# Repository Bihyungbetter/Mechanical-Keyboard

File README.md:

# Mechanical Keyboard

## Overview

This Mechanical Keyboard is a custom 75-key Alice mechanical keyboard built around a Raspberry Pi Pico / RP2040. It has a 5×15 key matrix, per-key SK6812 MINI-E RGB lighting, an EC11 rotary encoder with push switch, and a 128×32 I2C OLED display. I learned how to stitch together different parts, and I made this in hopes of a more ergonomic keyboard. 

I estimate I need 125$ for funding. Any extra funds will be returned to Hack Club

I do plan to make more unique designs and carvings in the CAD, but I want to first get it approved. School starts for me soon, so it's important for me to get this done asap :D. 
## Features

- 75 MX-compatible hot-swap switch positions
- RP2040 controller
- 75 SK6812 MINI-E addressable RGB LEDs
- Rotary encoder with volume control and mute push switch
- 128×32 I2C OLED display
- QMK firmware with a base layer and function/RGB layer

Onshape Link: https://cad.onshape.com/documents/8ad6bc956480bc630ab8271b/w/5b6e3b74d25b2afffc5b1596/e/df48eba2c3a944c445852ffe?renderMode=0&uiState=6ad977a7a138a0b5e7c4d2a0

## Repository layout

- `pcb/` — KiCad PCB, schematic, project, and lighting schematic
- `cad/` — The Entire CAD Assembly for the Keyboard
- `firmware/` — board-specific QMK sources and the compiled UF2
- `production/` — Gerber and drill files (gerber.zip) for PCB fabrication

## Pictures

## BOM

| Item | Part / Variant | Qty | Unit (USD) | Total (USD) | Link |
|---|---|---:|---:|---:|---|
| Raspberry Pi Pico | Raspberry Pi SC0915 (RP2040) | 1 | $4.59 | $4.59 | [DigiKey](https://www.digikey.com/en/products/detail/raspberry-pi/SC0915/13624793) |
| 1N4148 diode (DO-35) | onsemi 1N4148TA | 100 | $0.0336 | $3.36 | [DigiKey](https://www.digikey.com/en/products/detail/onsemi/1N4148TA/1532747) |
| Kailh MX hot-swap socket | Kailh CPG151101S11 | 80 | $0.10 | $8.00 | [KBDfans](https://kbdfans.com/products/mechanical-keyboard-switches-kailh-pcb-socket?variant=39678399381643) |
| EPOMAKER Creamy Jade switch | Creamy Jade Switch Set, 100 pcs (5-pin MX linear) | 1 | $19.99 | $19.99 | [EPOMAKER](https://epomaker.com/products/epomaker-creamy-jade-switch-set?variant=49273295831348) |
| SK6812 MINI-E RGB LED | SK-6812 MINI-E RGB LEDs, 25-pack | 4 | $5.99 | $23.96 | [Keebio](https://keeb.io/products/sk-6812-mini-e-rgb-leds-12-pack) |
| 0.91in 128x32 I2C OLED | HiLetgo 0.91in SSD1306 128x32 I2C | 1 | $6.49 | $6.49 | [Amazon](https://www.amazon.com/dp/B01N0KIVUX) |
| EC11 rotary encoder with push switch | Rotary Encoder - EC11, 20mm knurled shaft | 1 | $1.99 | $1.99 | [Keebio](https://keeb.io/products/rotary-encoder-ec11) |
| PCB-mount MX stabilizer | Cherry MX Stabilizer, 2u PCB Mount (2-pack) | 2 | $3.98 | $7.96 | [Keebio](https://keeb.io/products/cherry-mx-stabilizer?variant=39511997382750) |
| 100 nF capacitor (0805) | Samsung CL21B104KBCNNNC | 20 | $0.045 | $0.90 | [DigiKey](https://www.digikey.com/en/products/detail/samsung-electro-mechanics/CL21B104KBCNNNC/3886661) |
| 100 uF capacitor (1206, 10 V) | Murata GRM31CR61A107MEA8L | 2 | $0.55 | $1.10 | [DigiKey](https://www.digikey.com/en/products/detail/murata-electronics/GRM31CR61A107MEA8L/16033775) |
| 330 ohm resistor (0805) | Yageo RC0805FR-07330RL | 10 | $0.038 | $0.38 | [DigiKey](https://www.digikey.com/en/products/detail/yageo/RC0805FR-07330RL/727866) |
| Keycaps | Daylight PBT translucent keycaps, OEM profile, 135 keys - TopPrint White (keycaps only) | 1 | $11.15 | $11.15 | [AliExpress](https://www.aliexpress.us/item/3256810405041338.html) |
| PCB (5 pcs) | JLCPCB 360 x 155 mm, 2-layer, 1.6 mm FR-4 | 1 | $30.90 | $30.90 | [JLCPCB](https://cart.jlcpcb.com/quote) |
| **Total** | | | | **$120.77** | |

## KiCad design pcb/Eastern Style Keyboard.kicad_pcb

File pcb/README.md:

# PCB files

Open `Eastern Style Keyboard.kicad_pro` in KiCad. `Eastern Style Keyboard.kicad_pcb` is the board layout, and the two schematic files contain the main design and lighting-related circuitry.

The fabrication-ready outputs are in `../production/gerber.zip`.

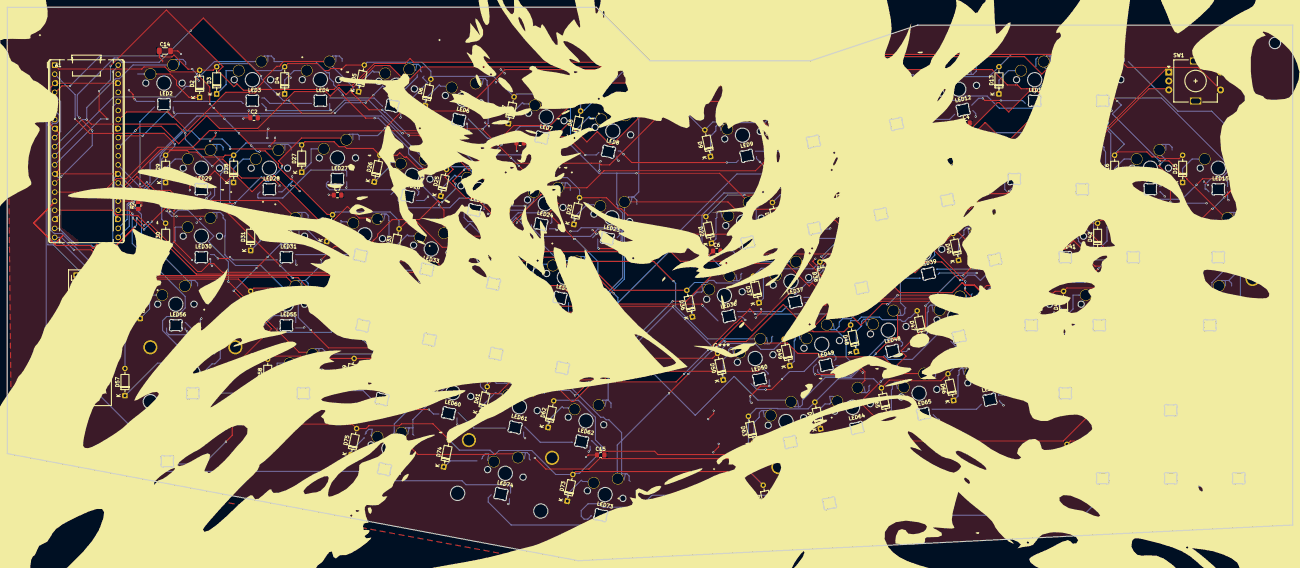
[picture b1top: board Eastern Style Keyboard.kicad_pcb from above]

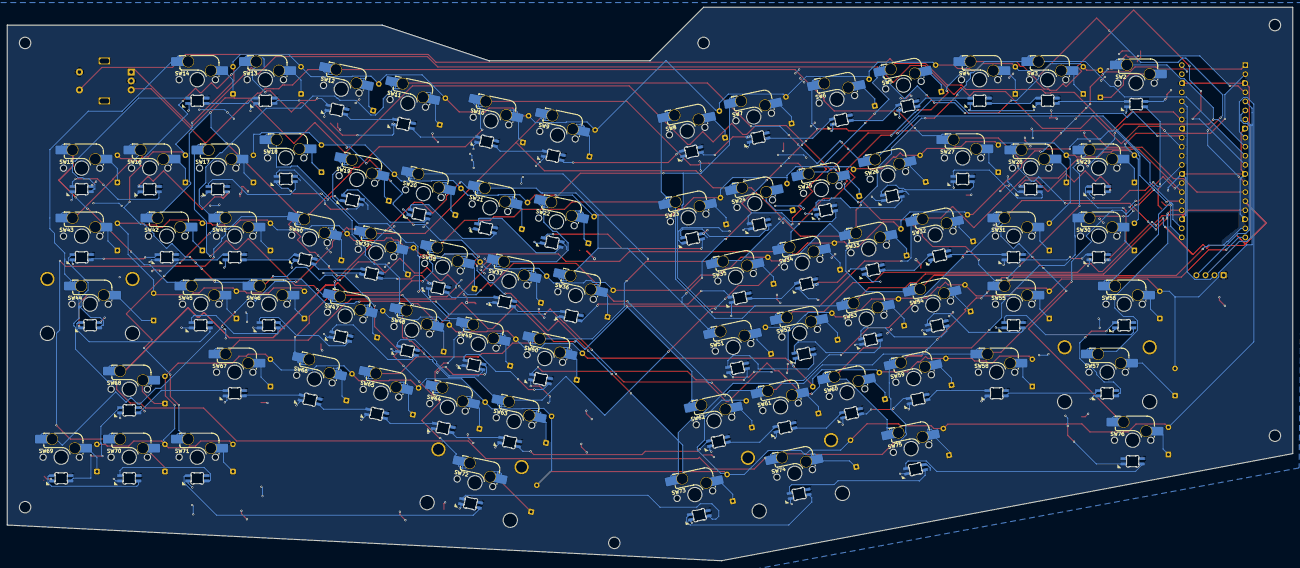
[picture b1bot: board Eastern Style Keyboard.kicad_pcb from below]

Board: 2 copper layers, 360.0 x 155.0 mm, 255 parts (75 on the bottom side), 179 nets.

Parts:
A1: RaspberryPi_Pico; RaspberryPi_Pico_Common_THT
C2, C3, C4, C5, C6, C7, C8, C9, C10, C11, C12, C13, C15, C16, C17: 100nF; C_0805_2012Metric_Pad1.18x1.45mm_HandSolder
C14: 100µF 10V; C_1206_3216Metric_Pad1.33x1.80mm_HandSolder
D2, D3, D4, D5, D6, D7, D8, D9, D10, D11, D12, D13, D14, D15, D16, D17, D18, D19, D20, D21, D22, D23, D24, D25, D26, D27, D28, D29, D30, D31, D32, D33, D34, D35, D36, D37, D38, D39, D40, D41, D42, D43, D44, D45, D46, D47, D48, D49, D50, D51, D52, D53, D54, D55, D56, D57, D58, D59, D60, D61, D62, D63, D64, D65, D66, D67, D68, D69, D70, D71, D72, D73, D74, D75, D76: 1N4148; D_DO-35_SOD27_P7.62mm_Horizontal
H1, H2, H3, H4, H5, H6: MountingHole; MountingHole_3.2mm_M3
LED2, LED3, LED4, LED5, LED6, LED7, LED8, LED9, LED10, LED11, LED12, LED13, LED14, LED15, LED16, LED17, LED18, LED19, LED20, LED21, LED22, LED23, LED24, LED25, LED26, LED27, LED28, LED29, LED30, LED31, LED32, LED33, LED34, LED35, LED36, LED37, LED38, LED39, LED40, LED41, LED42, LED43, LED44, LED45, LED46, LED47, LED48, LED49, LED50, LED51, LED52, LED53, LED54, LED55, LED56, LED57, LED58, LED59, LED60, LED61, LED62, LED63, LED64, LED65, LED66, LED67, LED68, LED69, LED70, LED71, LED72, LED73, LED74, LED75, LED76: SK6812MINI-E; SK6812MINI-E_fixed
R2: 330 Ω; R_0805_2012Metric_Pad1.20x1.40mm_HandSolder
S1: MX_stab; STAB_MX_P_2u
S2: MX_stab; STAB_MX_P_2.75u
S3, S4: MX_stab; STAB_MX_P_2.25u
SW1: RotaryEncoder_Switch; RotaryEncoder_Alps_EC11E-Switch_Vertical_H20mm
SW2, SW3, SW4, SW5, SW6, SW7, SW8, SW9, SW10, SW11, SW12, SW13, SW14, SW15, SW16, SW17, SW18, SW19, SW20, SW21, SW22, SW23, SW24, SW25, SW26, SW27, SW28, SW29, SW30, SW31, SW32, SW33, SW34, SW35, SW36, SW37, SW38, SW39, SW40, SW41, SW42, SW43, SW44, SW45, SW46, SW47, SW48, SW49, SW50, SW51, SW52, SW53, SW54, SW55, SW56, SW57, SW58, SW59, SW60, SW61, SW62, SW63, SW64, SW65, SW66, SW67, SW68, SW69, SW70, SW71, SW72, SW73, SW74, SW75, SW76: SW_Push; SW_MX_HS_CPG151101S11_1u
U1: ER_OLEDM0.91_1x-I2C

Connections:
+3.3V: A1.36 (3V3), U1.2 (VCC)
Column 0: A1.10 (GPIO7), SW2.2, SW17.2, SW32.2, SW47.2, SW62.2
Column 1: A1.11 (GPIO8), SW3.2, SW18.2, SW33.2, SW48.2, SW63.2
Column 2: A1.12 (GPIO9), SW4.2, SW19.2, SW34.2, SW49.2, SW64.2
Column 3: A1.14 (GPIO10), SW5.2, SW20.2, SW35.2, SW50.2, SW65.2
Column 4: A1.15 (GPIO11), SW6.2, SW21.2, SW36.2, SW51.2, SW66.2
Column 5: A1.16 (GPIO12), SW7.2, SW22.2, SW37.2, SW52.2, SW67.2
Column 6: A1.17 (GPIO13), SW8.2, SW23.2, SW38.2, SW53.2, SW68.2
Column 7: A1.19 (GPIO14), SW9.2, SW24.2, SW39.2, SW54.2, SW69.2
Column 8: A1.20 (GPIO15), SW10.2, SW25.2, SW40.2, SW55.2, SW70.2
Column 9: A1.22 (GPIO17), SW11.2, SW26.2, SW41.2, SW56.2, SW71.2
Column 10: A1.24 (GPIO18), SW12.2, SW27.2, SW42.2, SW57.2, SW72.2
Column 11: A1.25 (GPIO19), SW13.2, SW28.2, SW43.2, SW58.2, SW73.2
Column 12: A1.26 (GPIO20), SW14.2, SW29.2, SW44.2, SW59.2, SW74.2
Column 13: A1.27 (GPIO21), SW15.2, SW30.2, SW45.2, SW60.2, SW75.2
Column 14: A1.29 (GPIO22), SW16.2, SW31.2, SW46.2, SW61.2, SW76.2
GND: A1.3 (GND), A1.8 (GND), A1.13 (GND), A1.18 (GND), A1.23 (GND), A1.28 (GND), A1.38 (GND), C2.1, C3.1, C4.1, C5.1, C6.1, C7.1, C8.1, C9.1, C10.1, C11.1, C12.1, C13.1, C14.2, C15.1, C16.1, C17.1, LED2.1 (VSS), LED3.1 (VSS), LED4.1 (VSS), LED5.1 (VSS), LED6.1 (VSS), LED7.1 (VSS), LED8.1 (VSS), LED9.1 (VSS), LED10.1 (VSS), LED11.1 (VSS), LED12.1 (VSS), LED13.1 (VSS), LED14.1 (VSS), LED15.1 (VSS), LED16.1 (VSS), LED17.1 (VSS), LED18.1 (VSS), LED19.1 (VSS), LED20.1 (VSS), LED21.1 (VSS), LED22.1 (VSS), LED23.1 (VSS), LED24.1 (VSS), LED25.1 (VSS), LED26.1 (VSS), LED27.1 (VSS), LED28.1 (VSS), LED29.1 (VSS), LED30.1 (VSS), LED31.1 (VSS), LED32.1 (VSS), LED33.1 (VSS), LED34.1 (VSS), LED35.1 (VSS), LED36.1 (VSS), LED37.1 (VSS), LED38.1 (VSS), LED39.1 (VSS), LED40.1 (VSS), LED41.1 (VSS), LED42.1 (VSS), LED43.1 (VSS), LED44.1 (VSS), LED45.1 (VSS), LED46.1 (VSS), LED47.1 (VSS), LED48.1 (VSS), LED49.1 (VSS), LED50.1 (VSS), LED51.1 (VSS), LED52.1 (VSS), LED53.1 (VSS), LED54.1 (VSS), LED55.1 (VSS), LED56.1 (VSS), LED57.1 (VSS), LED58.1 (VSS), LED59.1 (VSS), LED60.1 (VSS), LED61.1 (VSS), LED62.1 (VSS), LED63.1 (VSS), LED64.1 (VSS), LED65.1 (VSS), LED66.1 (VSS), LED67.1 (VSS), LED68.1 (VSS), LED69.1 (VSS), LED70.1 (VSS), LED71.1 (VSS), LED72.1 (VSS), LED73.1 (VSS), LED74.1 (VSS), LED75.1 (VSS), LED76.1 (VSS), SW1.C, SW1.S2, U1.1 (GND)
KnobA: A1.31 (GPIO26_ADC0), SW1.A
KnobB: A1.32 (GPIO27_ADC1), SW1.B
LED Power: A1.40 (VBUS), C2.2, C3.2, C4.2, C5.2, C6.2, C7.2, C8.2, C9.2, C10.2, C11.2, C12.2, C13.2, C14.1, C15.2, C16.2, C17.2, LED2.3 (VDD), LED3.3 (VDD), LED4.3 (VDD), LED5.3 (VDD), LED6.3 (VDD), LED7.3 (VDD), LED8.3 (VDD), LED9.3 (VDD), LED10.3 (VDD), LED11.3 (VDD), LED12.3 (VDD), LED13.3 (VDD), LED14.3 (VDD), LED15.3 (VDD), LED16.3 (VDD), LED17.3 (VDD), LED18.3 (VDD), LED19.3 (VDD), LED20.3 (VDD), LED21.3 (VDD), LED22.3 (VDD), LED23.3 (VDD), LED24.3 (VDD), LED25.3 (VDD), LED26.3 (VDD), LED27.3 (VDD), LED28.3 (VDD), LED29.3 (VDD), LED30.3 (VDD), LED31.3 (VDD), LED32.3 (VDD), LED33.3 (VDD), LED34.3 (VDD), LED35.3 (VDD), LED36.3 (VDD), LED37.3 (VDD), LED38.3 (VDD), LED39.3 (VDD), LED40.3 (VDD), LED41.3 (VDD), LED42.3 (VDD), LED43.3 (VDD), LED44.3 (VDD), LED45.3 (VDD), LED46.3 (VDD), LED47.3 (VDD), LED48.3 (VDD), LED49.3 (VDD), LED50.3 (VDD), LED51.3 (VDD), LED52.3 (VDD), LED53.3 (VDD), LED54.3 (VDD), LED55.3 (VDD), LED56.3 (VDD), LED57.3 (VDD), LED58.3 (VDD), LED59.3 (VDD), LED60.3 (VDD), LED61.3 (VDD), LED62.3 (VDD), LED63.3 (VDD), LED64.3 (VDD), LED65.3 (VDD), LED66.3 (VDD), LED67.3 (VDD), LED68.3 (VDD), LED69.3 (VDD), LED70.3 (VDD), LED71.3 (VDD), LED72.3 (VDD), LED73.3 (VDD), LED74.3 (VDD), LED75.3 (VDD), LED76.3 (VDD)
Led S: A1.21 (GPIO16), R2.2
unnamed: A1.6 (GPIO4), U1.4 (SDA)
unnamed: A1.7 (GPIO5), U1.3 (SCL)
unnamed: D2.1 (K), SW2.1
unnamed: D3.1 (K), SW3.1
unnamed: D4.1 (K), SW4.1
unnamed: D5.1 (K), SW5.1
unnamed: D6.1 (K), SW6.1
unnamed: D7.1 (K), SW7.1
unnamed: D8.1 (K), SW8.1
unnamed: D9.1 (K), SW9.1
unnamed: D10.1 (K), SW10.1
unnamed: D11.1 (K), SW11.1
unnamed: D12.1 (K), SW12.1
unnamed: D13.1 (K), SW13.1
unnamed: D14.1 (K), SW14.1
unnamed: D15.1 (K), SW15.1
unnamed: D16.1 (K), SW16.1
unnamed: D17.1 (K), SW17.1
unnamed: D18.1 (K), SW18.1
unnamed: D19.1 (K), SW19.1
unnamed: D20.1 (K), SW20.1
unnamed: D21.1 (K), SW21.1
unnamed: D22.1 (K), SW22.1
unnamed: D23.1 (K), SW23.1
unnamed: D24.1 (K), SW24.1
unnamed: D25.1 (K), SW25.1
unnamed: D26.1 (K), SW26.1
unnamed: D27.1 (K), SW27.1
unnamed: D28.1 (K), SW28.1
unnamed: D29.1 (K), SW29.1
unnamed: D30.1 (K), SW30.1
unnamed: D31.1 (K), SW31.1
unnamed: D32.1 (K), SW32.1
unnamed: D33.1 (K), SW33.1
unnamed: D34.1 (K), SW34.1
unnamed: D35.1 (K), SW35.1
unnamed: D36.1 (K), SW36.1
unnamed: D37.1 (K), SW37.1
unnamed: D38.1 (K), SW38.1
unnamed: D39.1 (K), SW39.1
unnamed: D40.1 (K), SW40.1
unnamed: D41.1 (K), SW41.1
unnamed: D42.1 (K), SW42.1
unnamed: D43.1 (K), SW43.1
unnamed: D44.1 (K), SW44.1
unnamed: D45.1 (K), SW45.1
unnamed: D46.1 (K), SW46.1
unnamed: D47.1 (K), SW47.1
unnamed: D48.1 (K), SW48.1
unnamed: D49.1 (K), SW49.1
unnamed: D50.1 (K), SW50.1
unnamed: D51.1 (K), SW51.1
unnamed: D52.1 (K), SW52.1
unnamed: D53.1 (K), SW53.1
unnamed: D54.1 (K), SW54.1
unnamed: D55.1 (K), SW55.1
unnamed: D56.1 (K), SW56.1
unnamed: D57.1 (K), SW57.1
unnamed: D58.1 (K), SW58.1
unnamed: D59.1 (K), SW59.1
unnamed: D60.1 (K), SW60.1
unnamed: D61.1 (K), SW61.1
unnamed: D62.1 (K), SW62.1
unnamed: D63.1 (K), SW63.1
unnamed: D64.1 (K), SW64.1
unnamed: D65.1 (K), SW65.1
unnamed: D66.1 (K), SW66.1
unnamed: D67.1 (K), SW67.1
unnamed: D68.1 (K), SW68.1
unnamed: D69.1 (K), SW69.1
unnamed: D70.1 (K), SW70.1
unnamed: D71.1 (K), SW71.1
unnamed: D72.1 (K), SW72.1
unnamed: D73.1 (K), SW73.1
unnamed: D74.1 (K), SW74.1
unnamed: D75.1 (K), SW75.1
unnamed: D76.1 (K), SW76.1
unnamed: LED2.2 (DIN), R2.1
unnamed: LED2.4 (DOUT), LED3.2 (DIN)
unnamed: LED3.4 (DOUT), LED4.2 (DIN)
unnamed: LED4.4 (DOUT), LED5.2 (DIN)
unnamed: LED5.4 (DOUT), LED6.2 (DIN)
unnamed: LED6.4 (DOUT), LED7.2 (DIN)
unnamed: LED7.4 (DOUT), LED8.2 (DIN)
unnamed: LED8.4 (DOUT), LED9.2 (DIN)
unnamed: LED9.4 (DOUT), LED10.2 (DIN)
unnamed: LED10.4 (DOUT), LED11.2 (DIN)
unnamed: LED11.4 (DOUT), LED12.2 (DIN)
unnamed: LED12.4 (DOUT), LED13.2 (DIN)
unnamed: LED13.4 (DOUT), LED14.2 (DIN)
unnamed: LED14.4 (DOUT), LED15.2 (DIN)
unnamed: LED15.4 (DOUT), LED16.2 (DIN)
unnamed: LED16.4 (DOUT), LED17.2 (DIN)
unnamed: LED17.4 (DOUT), LED18.2 (DIN)
unnamed: LED18.4 (DOUT), LED19.2 (DIN)
unnamed: LED19.4 (DOUT), LED20.2 (DIN)
unnamed: LED20.4 (DOUT), LED21.2 (DIN)
unnamed: LED21.4 (DOUT), LED22.2 (DIN)
unnamed: LED22.4 (DOUT), LED23.2 (DIN)
unnamed: LED23.4 (DOUT), LED24.2 (DIN)
unnamed: LED24.4 (DOUT), LED25.2 (DIN)
unnamed: LED25.4 (DOUT), LED26.2 (DIN)
unnamed: LED26.4 (DOUT), LED27.2 (DIN)
unnamed: LED27.4 (DOUT), LED28.2 (DIN)
unnamed: LED28.4 (DOUT), LED29.2 (DIN)
unnamed: LED29.4 (DOUT), LED30.2 (DIN)
unnamed: LED30.4 (DOUT), LED31.2 (DIN)
unnamed: LED31.4 (DOUT), LED32.2 (DIN)
unnamed: LED32.4 (DOUT), LED33.2 (DIN)
unnamed: LED33.4 (DOUT), LED34.2 (DIN)
unnamed: LED34.4 (DOUT), LED35.2 (DIN)
unnamed: LED35.4 (DOUT), LED36.2 (DIN)
unnamed: LED36.4 (DOUT), LED37.2 (DIN)
unnamed: LED37.4 (DOUT), LED38.2 (DIN)
unnamed: LED38.4 (DOUT), LED39.2 (DIN)
unnamed: LED39.4 (DOUT), LED40.2 (DIN)
unnamed: LED40.4 (DOUT), LED41.2 (DIN)
unnamed: LED41.4 (DOUT), LED42.2 (DIN)
unnamed: LED42.4 (DOUT), LED43.2 (DIN)
unnamed: LED43.4 (DOUT), LED44.2 (DIN)
unnamed: LED44.4 (DOUT), LED45.2 (DIN)
unnamed: LED45.4 (DOUT), LED46.2 (DIN)
unnamed: LED46.4 (DOUT), LED47.2 (DIN)
unnamed: LED47.4 (DOUT), LED48.2 (DIN)
unnamed: LED48.4 (DOUT), LED49.2 (DIN)
unnamed: LED49.4 (DOUT), LED50.2 (DIN)
unnamed: LED50.4 (DOUT), LED51.2 (DIN)
unnamed: LED51.4 (DOUT), LED52.2 (DIN)
unnamed: LED52.4 (DOUT), LED53.2 (DIN)
unnamed: LED53.4 (DOUT), LED54.2 (DIN)
unnamed: LED54.4 (DOUT), LED55.2 (DIN)
unnamed: LED55.4 (DOUT), LED56.2 (DIN)
unnamed: LED56.4 (DOUT), LED57.2 (DIN)
unnamed: LED57.4 (DOUT), LED58.2 (DIN)
unnamed: LED58.4 (DOUT), LED59.2 (DIN)
unnamed: LED59.4 (DOUT), LED60.2 (DIN)
unnamed: LED60.4 (DOUT), LED61.2 (DIN)
unnamed: LED61.4 (DOUT), LED62.2 (DIN)
unnamed: LED62.4 (DOUT), LED63.2 (DIN)
unnamed: LED63.4 (DOUT), LED64.2 (DIN)
unnamed: LED64.4 (DOUT), LED65.2 (DIN)
unnamed: LED65.4 (DOUT), LED66.2 (DIN)
unnamed: LED66.4 (DOUT), LED67.2 (DIN)
unnamed: LED67.4 (DOUT), LED68.2 (DIN)
unnamed: LED68.4 (DOUT), LED69.2 (DIN)
unnamed: LED69.4 (DOUT), LED70.2 (DIN)
unnamed: LED70.4 (DOUT), LED71.2 (DIN)
unnamed: LED71.4 (DOUT), LED72.2 (DIN)
unnamed: LED72.4 (DOUT), LED73.2 (DIN)
unnamed: LED73.4 (DOUT), LED74.2 (DIN)
unnamed: LED74.4 (DOUT), LED75.2 (DIN)
unnamed: LED75.4 (DOUT), LED76.2 (DIN)
Push: A1.34 (GPIO28_ADC2), SW1.S1
Row 0: A1.1 (GPIO0), D2.2 (A), D3.2 (A), D4.2 (A), D5.2 (A), D6.2 (A), D7.2 (A), D8.2 (A), D9.2 (A), D10.2 (A), D11.2 (A), D12.2 (A), D13.2 (A), D14.2 (A), D15.2 (A), D16.2 (A)
Row 1: A1.2 (GPIO1), D17.2 (A), D18.2 (A), D19.2 (A), D20.2 (A), D21.2 (A), D22.2 (A), D23.2 (A), D24.2 (A), D25.2 (A), D26.2 (A), D27.2 (A), D28.2 (A), D29.2 (A), D30.2 (A), D31.2 (A)
Row 2: A1.4 (GPIO2), D32.2 (A), D33.2 (A), D34.2 (A), D35.2 (A), D36.2 (A), D37.2 (A), D38.2 (A), D39.2 (A), D40.2 (A), D41.2 (A), D42.2 (A), D43.2 (A), D44.2 (A), D45.2 (A), D46.2 (A)
Row 3: A1.5 (GPIO3), D47.2 (A), D48.2 (A), D49.2 (A), D50.2 (A), D51.2 (A), D52.2 (A), D53.2 (A), D54.2 (A), D55.2 (A), D56.2 (A), D57.2 (A), D58.2 (A), D59.2 (A), D60.2 (A), D61.2 (A)
Row 4: A1.9 (GPIO6), D62.2 (A), D63.2 (A), D64.2 (A), D65.2 (A), D66.2 (A), D67.2 (A), D68.2 (A), D69.2 (A), D70.2 (A), D71.2 (A), D72.2 (A), D73.2 (A), D74.2 (A), D75.2 (A), D76.2 (A)

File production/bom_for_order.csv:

Designator,Footprint,Quantity,Value,LCSC Part #
A1,RaspberryPi_Pico_Common_THT,1,RaspberryPi_Pico,
"C10, C11, C12, C13, C15, C16, C17, C2, C3, C4, C5, C6, C7, C8, C9",0805,15,100nF,
C14,1206,1,100µF 10V,
"D10, D11, D12, D13, D14, D15, D16, D17, D18, D19, D2, D20, D21, D22, D23, D24, D25, D26, D27, D28, D29, D3, D30, D31, D32, D33, D34, D35, D36, D37, D38, D39, D4, D40, D41, D42, D43, D44, D45, D46, D47, D48, D49, D5, D50, D51, D52, D53, D54, D55, D56, D57, D58, D59, D6, D60, D61, D62, D63, D64, D65, D66, D67, D68, D69, D7, D70, D71, D72, D73, D74, D75, D76, D8, D9",D_DO-35_SOD27_P7.62mm_Horizontal,75,1N4148,
"LED10, LED11, LED12, LED13, LED14, LED15, LED16, LED17, LED18, LED19, LED2, LED20, LED21, LED22, LED23, LED24, LED25, LED26, LED27, LED28, LED29, LED3, LED30, LED31, LED32, LED33, LED34, LED35, LED36, LED37, LED38, LED39, LED4, LED40, LED41, LED42, LED43, LED44, LED45, LED46, LED47, LED48, LED49, LED5, LED50, LED51, LED52, LED53, LED54, LED55, LED56, LED57, LED58, LED59, LED6, LED60, LED61, LED62, LED63, LED64, LED65, LED66, LED67, LED68, LED69, LED7, LED70, LED71, LED72, LED73, LED74, LED75, LED76, LED8, LED9",SK6812MINI-E_fixed,75,SK6812MINI-E,
R2,0805,1,330 Ω,
S1,STAB_MX_P_2u,1,MX_stab,
S2,STAB_MX_P_2.75u,1,MX_stab,
"S3, S4",STAB_MX_P_2.25u,2,MX_stab,
SW1,RotaryEncoder_Alps_EC11E-Switch_Vertical_H20mm,1,RotaryEncoder_Switch,
"SW10, SW11, SW12, SW13, SW14, SW15, SW16, SW17, SW18, SW19, SW2, SW20, SW21, SW22, SW23, SW24, SW25, SW26, SW27, SW28, SW29, SW3, SW30, SW31, SW32, SW33, SW34, SW35, SW36, SW37, SW38, SW39, SW4, SW40, SW41, SW42, SW43, SW44, SW45, SW46, SW47, SW48, SW49, SW5, SW50, SW51, SW52, SW53, SW54, SW55, SW56, SW57, SW58, SW59, SW6, SW60, SW61, SW62, SW63, SW64, SW65, SW66, SW67, SW68, SW69, SW7, SW70, SW71, SW72, SW73, SW74, SW75, SW76, SW8, SW9",SW_MX_HS_CPG151101S11_1u,75,SW_Push,
U1,ER_OLEDM0.91_1x-I2C,1,ER_OLEDM0.91_1x-I2C,
PURCHASE-1,,100,Kailh CPG151101S11 hot-swap sockets,https://www.aliexpress.us/item/3256805961019213.html
PURCHASE-2,,100,EPOMAKER Creamy Jade 5-pin linear switches,https://www.aliexpress.us/item/3256808961367250.html
PURCHASE-3,,1,3mm Poron keyboard foam - custom easy-cut option,https://www.aliexpress.us/item/3256812626509369.html
PURCHASE-4,,1,3mm Poron keyboard foam - layout option,https://www.aliexpress.us/item/3256803657562583.html
PURCHASE-5,,50,DIN912 A2-70 stainless socket-head screws - confirm size,https://www.aliexpress.us/item/3256811659626164.html
PURCHASE-6,,100,Brass hot-melt heat-set insert nuts - confirm M-size variant,https://www.aliexpress.us/item/2255800046543591.html
PURCHASE-7,,1,Keychron double-shot PBT Cherry full-set keycaps - Hacker,https://www.keychron.com/products/double-shot-pbt-cherry-ful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
